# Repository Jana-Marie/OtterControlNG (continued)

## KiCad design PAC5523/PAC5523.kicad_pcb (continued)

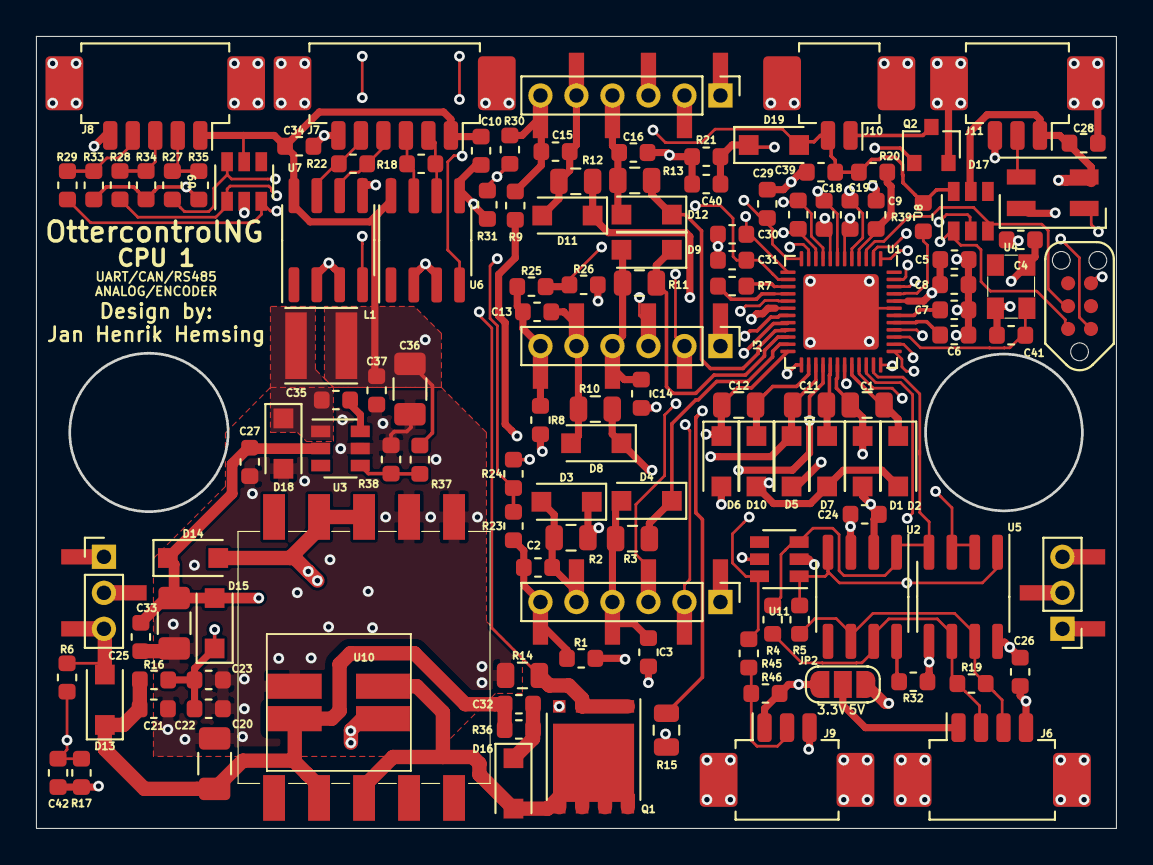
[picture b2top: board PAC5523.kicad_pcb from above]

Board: 4 copper layers, 59.9 x 43.9 mm, 128 parts (0 on the bottom side), 82 nets.

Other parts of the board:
C4, C27, C35, C37: 100n; C_0603_1608Metric
C36: 10u; C_1206_3216Metric
D17: SK6812MINI; LED_SK6812MINI_PLCC4_3.5x3.5mm_P1.75mm
D18: SS310; D_SOD-123F
L1: 4u7; L_Taiyo-Yuden_MD-4040
R32: 4k3; R_0603_1608Metric
R37: 47k; R_0603_1608Metric
R38: 9k1; R_0603_1608Metric
U2: MAX3051; SOIC-8_3.9x4.9mm_P1.27mm
U3: ACT4088; SOT-23-6
U5: RS485; SOIC-8_3.9x4.9mm_P1.27mm
U6: ENCODER A; SOIC-8_3.9x4.9mm_P1.27mm
U7: ENCODER B; SOIC-8_3.9x4.9mm_P1.27mm
U8, U9, U11: USBLC6-4; SOT-23-6

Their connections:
+5V: C36.1, C37.1, D17.4, L1.2, R37.1, U2.3, U5.8, U6.8, U7.8, U8.5, U9.5, U11.5; also elsewhere on the board
Ain: U11.6; also elsewhere on the board
CANH: U2.7, U5.6; also elsewhere on the board
CANL: U2.6, U5.7; also elsewhere on the board
CANRX: U2.4, U5.1, U11.1; also elsewhere on the board
CANTX: U2.1, U5.4, U11.3; also elsewhere on the board
ENC_A: U6.4; also elsewhere on the board
ENC_A_A: U6.6; also elsewhere on the board
ENC_A_B: U6.7; also elsewhere on the board
ENC_B: U7.4; also elsewhere on the board
ENC_B_A: U7.6; also elsewhere on the board
ENC_B_B: U7.7; also elsewhere on the board
GND: C4.2, C27.2, C36.2, C37.2, D17.2, D18.2, R32.2, R38.2, U2.2, U3.5, U5.5, U6.2, U6.3, U6.5, U7.2, U7.3, U7.5, U8.2, U9.2, U11.2; also elsewhere on the board
HALL1: U9.6; also elsewhere on the board
HALL2: U9.1; also elsewhere on the board
HALL3: U9.3; also elsewhere on the board
NTC_EXT: U8.6; also elsewhere on the board
unnamed: C35.1, U3.6
unnamed: C35.2, D18.1, L1.1, U3.1
unnamed: R32.1, U2.8
unnamed: R37.2, R38.1, U3.4
RS485RXTX: U5.2, U5.3; also elsewhere on the board
SK6812: D17.3; also elsewhere on the board
SK6812_OUT: D17.1; also elsewhere on the board
SWDCL: U8.3; also elsewhere on the board
SWDIO: U8.1; also elsewhere on the board
VIO: C4.1; also elsewhere on the board
VP: C27.1, U3.2; also elsewhere on the board

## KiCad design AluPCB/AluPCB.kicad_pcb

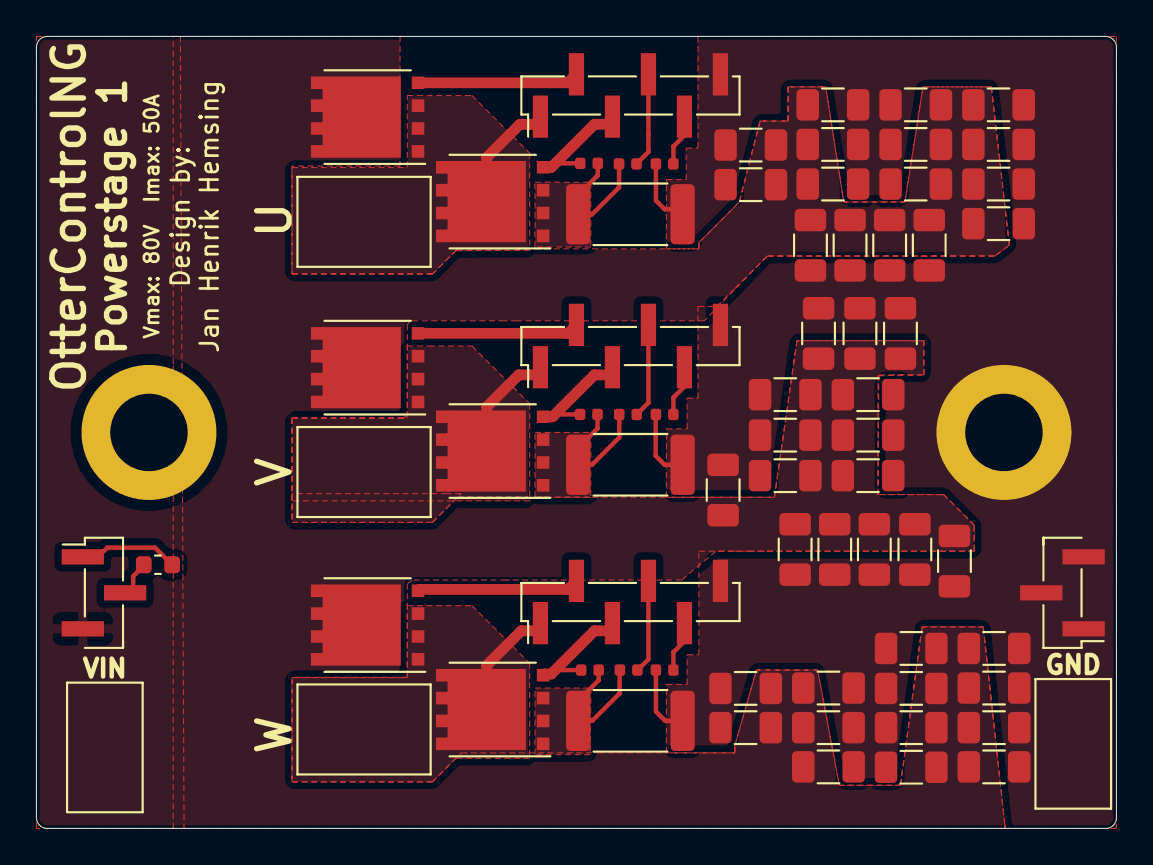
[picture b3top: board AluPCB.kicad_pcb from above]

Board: 2 copper layers, 60.0 x 44.0 mm, 70 parts (0 on the bottom side), 22 nets.

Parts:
C1, C2, C3, C5, C7, C9, C11, C14, C15, C20, C21, C22, C23, C25, C26, C28, C29, C31, C32, C33, C34, C35, C36, C37, C38, C39, C40, C41, C42, C43, C44, C45, C47, C48, C49, C50, C52, C53, C54, C55, C56, C58, C59, C60: 2u2; C_1206_3216Metric
H1, H2: MountingHole_Pad; MountingHole_4.3mm_M4_DIN965_Pad
J1, J2, J3: CON_U; PinHeader_1x06_P2.00mm_Vertical_SMD_Pin1Left
J4: GND; PinHeader_1x03_P2.00mm_Vertical_SMD_Pin1Left
J5: VIN; PinHeader_1x03_P2.00mm_Vertical_SMD_Pin1Left
Q1, Q2, Q3, Q4, Q5, Q6: AON6276; VSONP-8-1EP_5x6_P1.27mm
R1, R4, R7: R001; R_2512_6332Metric
R2, R3, R5, R6, R8, R9: 100; R_0402_1005Metric
R10, R11, R12: 10k; R_0402_1005Metric
TH1: 10k; R_0603_1608Metric

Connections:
GND: C1.2, C2.2, C3.2, C5.2, C7.2, C9.2, C11.2, C14.2, C15.2, C20.2, C21.2, C22.2, C23.2, C25.2, C26.2, C28.2, C29.2, C31.2, C32.2, C33.2, C34.2, C35.2, C36.2, C37.2, C38.2, C39.2, C40.2, C41.2, C42.2, C43.2, C44.2, C45.2, C47.2, C48.2, C49.2, C50.2, C52.2, C53.2, C54.2, C55.2, C56.2, C58.2, C59.2, C60.2, H2.1, J1.6, J2.6, J3.6, J4.1, J4.2, J4.3, R1.2, R3.2, R4.2, R6.2, R7.2, R9.2
GUH: J1.2, Q1.2
GUL: J1.3, Q2.2, R10.2
GVH: J2.2, Q3.2
GVL: J2.3, Q4.2, R11.2
GWH: J3.2, Q5.2
GWL: J3.3, Q6.2, R12.2
IUH: J1.4, R2.1
IUL: J1.5, R3.1
IVH: J2.4, R5.1
IVL: J2.5, R6.1
IWH: J3.4, R8.1
IWL: J3.5, R9.1
unnamed: J5.1, TH1.2
unnamed: J5.2, TH1.1
unnamed: Q2.1, R1.1, R2.2, R10.1
unnamed: Q4.1, R4.1, R5.2, R11.1
unnamed: Q6.1, R7.1, R8.2, R12.1
U: J1.1, Q1.1, Q2.3
V: J2.1, Q3.1, Q4.3
VIN: C1.1, C2.1, C3.1, C5.1, C7.1, C9.1, C11.1, C14.1, C15.1, C20.1, C21.1, C22.1, C23.1, C25.1, C26.1, C28.1, C29.1, C31.1, C32.1, C33.1, C34.1, C35.1, C36.1, C37.1, C38.1, C39.1, C40.1, C41.1, C42.1, C43.1, C44.1, C45.1, C47.1, C48.1, C49.1, C50.1, C52.1, C53.1, C54.1, C55.1, C56.1, C58.1, C59.1, C60.1, J5.3, Q1.3, Q3.3, Q5.3
W: J3.1, Q5.1, Q6.3

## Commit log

2019-04-28 added gitignore
2019-04-28 updated connectors
2019-04-28 schematic cleanup, added PDF
2019-04-28 updated schematic
2019-04-28 moved files
2019-04-28 aluPCB V1
2019-04-28 finished AluPCB Power Stage 1, added images
2019-05-05 updated PCB, changed size to 44x50mm
2019-05-05 finished ALUpcb
2019-05-14 finalized Powerstage, ordered PCBs
2019-05-14 added Encoder,LED,NTC
2019-05-15 placement almost done
2019-05-15 routing 60% done
2019-05-20 finalized board, silkscreen needs some work
2019-05-20 finalized silkscreen
2019-05-22 finalized silkscreen, generated gerber
2019-07-11 added boms
2019-07-11 added notes
2019-07-11 added images
2019-07-22 added gerber
2019-11-15 added stm32G431
2019-11-17 updated files
2019-12-10 updated pcb
2019-12-15 remaned files
2019-12-15 removed old files
2019-12-15 updated layout
2020-01-31 added image
2020-01-31 added firmware submodule
